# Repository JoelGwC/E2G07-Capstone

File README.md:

# E2G07-Capstone

This is an online repository for intelligent equipment management that will be our 4th year capstone project.

There are two dashboards:
User & Admin

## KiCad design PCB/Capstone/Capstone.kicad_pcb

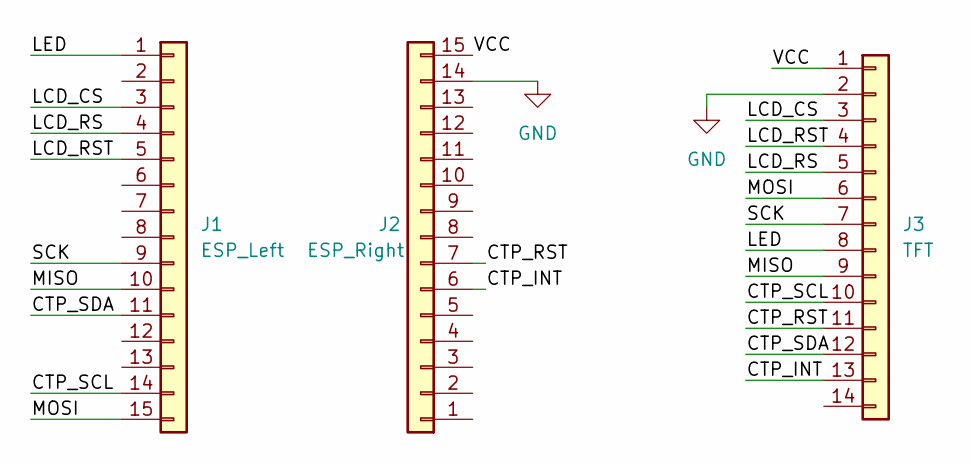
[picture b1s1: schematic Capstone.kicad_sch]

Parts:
J1: ESP_Left; PinSocket_1x15_P2.54mm_Vertical
J2: ESP_Right; PinSocket_1x15_P2.54mm_Vertical
J3: TFT; PinSocket_1x14_P2.54mm_Vertical

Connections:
/CTP_INT: J2.6, J3.13
/CTP_RST: J2.7, J3.11
/CTP_SCL: J1.14, J3.10
/CTP_SDA: J1.11, J3.12
/LCD_CS: J1.3, J3.3
/LCD_RS: J1.4, J3.5
/LCD_RST: J1.5, J3.4
/LED: J1.1, J3.8
/MISO: J1.10, J3.9
/MOSI: J1.15, J3.6
/SCK: J1.9, J3.7
/VCC: J2.15, J3.1
GND: J2.14, J3.2

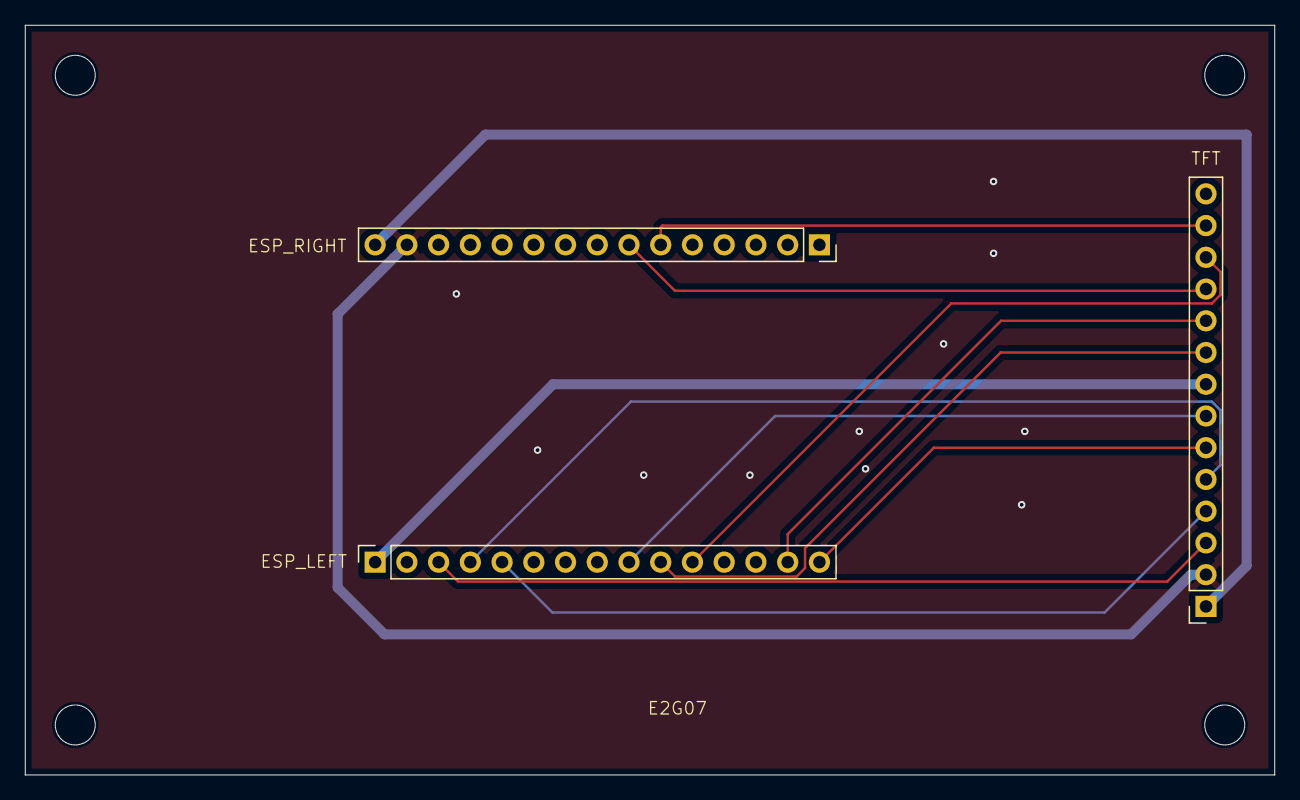
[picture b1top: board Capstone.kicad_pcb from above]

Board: 2 copper layers, 100.0 x 60.0 mm, 3 parts (0 on the bottom side), 13 nets.

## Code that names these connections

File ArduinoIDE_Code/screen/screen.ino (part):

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// esp_now_peer_info_t peerInfo;

// Hardware Pins
#define CTP_SDA          21
#define CTP_SCL          22
#define CTP_RST          33
#define FT6336U_ADDR     0x38

// ================= COLORS & STYLES =================
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 
  Wire.begin(CTP_SDA, CTP_SCL);
  Wire.setTimeOut(1000);
  pinMode(CTP_RST, OUTPUT);
  digitalWrite(CTP_RST, LOW);
  delay(10);
  digitalWrite(CTP_RST, HIGH);
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
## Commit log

2025-11-13 firebase initialisation
2025-11-13 changed folder name
2025-12-03 index2
2025-12-03 pushing to main instead on master
2025-12-03 updated the index.html
2025-12-03 removed unused file
2025-12-03 changed file name
2025-12-08 updated index
2025-12-08 working HTML and ESP32
2025-12-08 update ESP32 code
2025-12-08 removed index2.html
2025-12-09 added contact card at footer
2025-12-09 Optimise mobile experice
2025-12-09 changed NTP time pool
2025-12-09 Added custom duration functionality
2025-12-10 added admin dashboard
2025-12-10 merged Umar branch
2025-12-11 updated the admin dashboard and the esp32 code
2025-12-11 included schedule view
2025-12-12 updated admin dashboard
2025-12-15 updated admin.html and added screen.ino
2025-12-16 using ESPNow for the ESP code
2025-12-16 PCB for screen and ESP32
2025-12-19 added link to admin dashboard from user side
2025-12-21 added search function
2025-12-22 updated export CSV function
2025-12-23 updated all code
2025-12-23 send email when revoked
2026-01-03 changed WiFi credentials
2026-01-03 Added PCB components
2026-01-08 fixed admin dashboard for mobile devices
2026-01-09 backup plan
2026-01-10 changed icons
2026-01-10 checkin window
2026-01-13 latest version
